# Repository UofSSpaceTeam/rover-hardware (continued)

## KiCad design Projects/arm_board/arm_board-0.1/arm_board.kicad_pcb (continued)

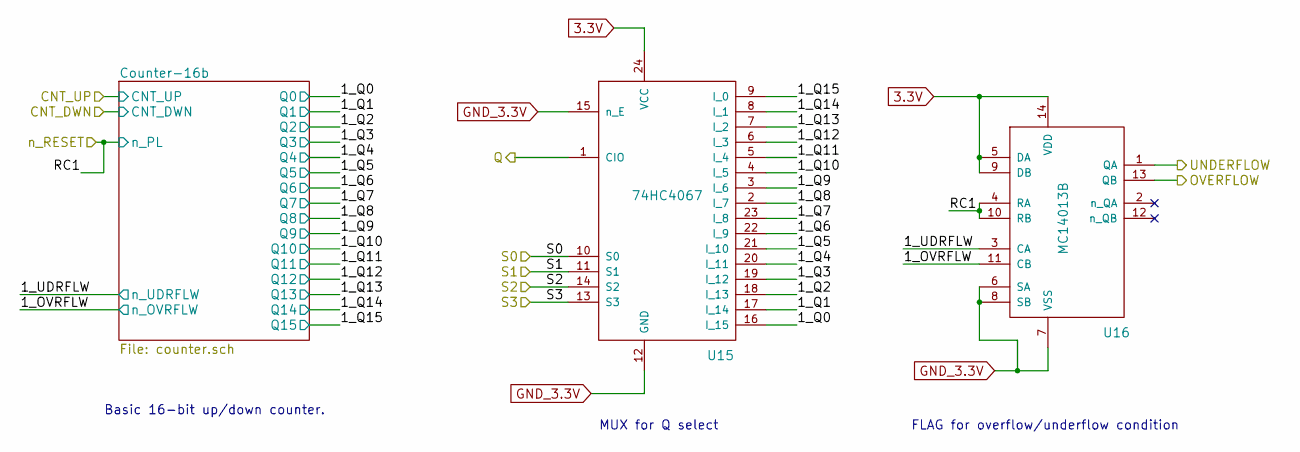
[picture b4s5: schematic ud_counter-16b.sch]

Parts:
U15: 74HC4067; SOIC-24
U49: MC14013B; SOIC-14_N

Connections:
/VNH3SP30 Motor SS 1/16-bit UD Counter/Counter-16b/Q0: U15.16 (I_15); also elsewhere on the board
/VNH3SP30 Motor SS 1/16-bit UD Counter/Counter-16b/Q1: U15.17 (I_14); also elsewhere on the board
/VNH3SP30 Motor SS 1/16-bit UD Counter/Counter-16b/Q2: U15.18 (I_13); also elsewhere on the board
/VNH3SP30 Motor SS 1/16-bit UD Counter/Counter-16b/Q3: U15.19 (I_12); also elsewhere on the board
/VNH3SP30 Motor SS 1/16-bit UD Counter/Counter-16b/Q4: U15.20 (I_11); also elsewhere on the board
/VNH3SP30 Motor SS 1/16-bit UD Counter/Counter-16b/Q5: U15.21 (I_10); also elsewhere on the board
/VNH3SP30 Motor SS 1/16-bit UD Counter/Counter-16b/Q6: U15.22 (I_9); also elsewhere on the board
/VNH3SP30 Motor SS 1/16-bit UD Counter/Counter-16b/Q7: U15.23 (I_8); also elsewhere on the board
/VNH3SP30 Motor SS 1/16-bit UD Counter/Counter-16b/Q8: U15.2 (I_7); also elsewhere on the board
/VNH3SP30 Motor SS 1/16-bit UD Counter/Counter-16b/Q9: U15.3 (I_6); also elsewhere on the board
/VNH3SP30 Motor SS 1/16-bit UD Counter/Counter-16b/Q10: U15.4 (I_5); also elsewhere on the board
/VNH3SP30 Motor SS 1/16-bit UD Counter/Counter-16b/Q11: U15.5 (I_4); also elsewhere on the board
/VNH3SP30 Motor SS 1/16-bit UD Counter/Counter-16b/Q12: U15.6 (I_3); also elsewhere on the board
/VNH3SP30 Motor SS 1/16-bit UD Counter/Counter-16b/Q13: U15.7 (I_2); also elsewhere on the board
/VNH3SP30 Motor SS 1/16-bit UD Counter/Counter-16b/Q14: U15.8 (I_1); also elsewhere on the board
/VNH3SP30 Motor SS 1/16-bit UD Counter/Counter-16b/Q15: U15.9 (I_0); also elsewhere on the board
/VNH3SP30 Motor SS 1/CNT_S0: U15.10 (S0); also elsewhere on the board
/VNH3SP30 Motor SS 1/CNT_S1: U15.11 (S1); also elsewhere on the board
/VNH3SP30 Motor SS 1/CNT_S2: U15.14 (S2); also elsewhere on the board
/VNH3SP30 Motor SS 1/CNT_S3: U15.13 (S3); also elsewhere on the board
/VNH3SP30 Motor SS 1/Q_CNT: U15.1 (CIO); also elsewhere on the board
/vnh3sp30_motorLinac_ss/16-bit UD Counter/Counter-16b/n_OVRFLW: U49.11 (CB); also elsewhere on the board
/vnh3sp30_motorLinac_ss/16-bit UD Counter/Counter-16b/n_UDRFLW: U49.3 (CA); also elsewhere on the board
/vnh3sp30_motorLinac_ss/CNT_OVRFLW: U49.13 (QB); also elsewhere on the board
/vnh3sp30_motorLinac_ss/CNT_UDRFLW: U49.1 (QA); also elsewhere on the board
/vnh3sp30_motorLinac_ss/n_CNT_RESET: U49.4 (RA), U49.10 (RB); also elsewhere on the board

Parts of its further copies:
U16, U23, U30, U37, U51: MC14013B; SOIC-14_N
U22, U29, U36, U43, U50: 74HC4067; SOIC-24

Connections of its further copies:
/VNH3SP30 Motor SS 1/16-bit UD Counter/Counter-16b/n_OVRFLW: U16.11 (CB); also elsewhere on the board
/VNH3SP30 Motor SS 1/16-bit UD Counter/Counter-16b/n_UDRFLW: U16.3 (CA); also elsewhere on the board
/VNH3SP30 Motor SS 1/CNT_OVRFLW: U16.13 (QB); also elsewhere on the board
/VNH3SP30 Motor SS 1/CNT_S0: U22.10 (S0), U29.10 (S0), U36.10 (S0), U43.10 (S0), U50.10 (S0); also elsewhere on the board
/VNH3SP30 Motor SS 1/CNT_S1: U22.11 (S1), U29.11 (S1), U36.11 (S1), U43.11 (S1), U50.11 (S1); also elsewhere on the board
/VNH3SP30 Motor SS 1/CNT_S2: U22.14 (S2), U29.14 (S2), U36.14 (S2), U43.14 (S2), U50.14 (S2); also elsewhere on the board
/VNH3SP30 Motor SS 1/CNT_S3: U22.13 (S3), U29.13 (S3), U36.13 (S3), U43.13 (S3), U50.13 (S3); also elsewhere on the board
/VNH3SP30 Motor SS 1/CNT_UDRFLW: U16.1 (QA); also elsewhere on the board
/VNH3SP30 Motor SS 1/n_CNT_RESET: U16.4 (RA), U16.10 (RB); also elsewhere on the board
/VNH3SP30 Motor SS 2/16-bit UD Counter/Counter-16b/Q0: U50.16 (I_15); also elsewhere on the board
/VNH3SP30 Motor SS 2/16-bit UD Counter/Counter-16b/Q1: U50.17 (I_14); also elsewhere on the board
/VNH3SP30 Motor SS 2/16-bit UD Counter/Counter-16b/Q2: U50.18 (I_13); also elsewhere on the board
/VNH3SP30 Motor SS 2/16-bit UD Counter/Counter-16b/Q3: U50.19 (I_12); also elsewhere on the board
/VNH3SP30 Motor SS 2/16-bit UD Counter/Counter-16b/Q4: U50.20 (I_11); also elsewhere on the board
/VNH3SP30 Motor SS 2/16-bit UD Counter/Counter-16b/Q5: U50.21 (I_10); also elsewhere on the board
/VNH3SP30 Motor SS 2/16-bit UD Counter/Counter-16b/Q6: U50.22 (I_9); also elsewhere on the board
/VNH3SP30 Motor SS 2/16-bit UD Counter/Counter-16b/Q7: U50.23 (I_8); also elsewhere on the board
/VNH3SP30 Motor SS 2/16-bit UD Counter/Counter-16b/Q8: U50.2 (I_7); also elsewhere on the board
/VNH3SP30 Motor SS 2/16-bit UD Counter/Counter-16b/Q9: U50.3 (I_6); also elsewhere on the board
/VNH3SP30 Motor SS 2/16-bit UD Counter/Counter-16b/Q10: U50.4 (I_5); also elsewhere on the board
/VNH3SP30 Motor SS 2/16-bit UD Counter/Counter-16b/Q11: U50.5 (I_4); also elsewhere on the board
/VNH3SP30 Motor SS 2/16-bit UD Counter/Counter-16b/Q12: U50.6 (I_3); also elsewhere on the board
/VNH3SP30 Motor SS 2/16-bit UD Counter/Counter-16b/Q13: U50.7 (I_2); also elsewhere on the board
/VNH3SP30 Motor SS 2/16-bit UD Counter/Counter-16b/Q14: U50.8 (I_1); also elsewhere on the board
/VNH3SP30 Motor SS 2/16-bit UD Counter/Counter-16b/Q15: U50.9 (I_0); also elsewhere on the board
/VNH3SP30 Motor SS 2/16-bit UD Counter/Counter-16b/n_OVRFLW: U51.11 (CB); also elsewhere on the board
/VNH3SP30 Motor SS 2/16-bit UD Counter/Counter-16b/n_UDRFLW: U51.3 (CA); also elsewhere on the board
/VNH3SP30 Motor SS 2/CNT_OVRFLW: U51.13 (QB); also elsewhere on the board
/VNH3SP30 Motor SS 2/CNT_UDRFLW: U51.1 (QA); also elsewhere on the board
/VNH3SP30 Motor SS 2/Q_CNT: U50.1 (CIO); also elsewhere on the board
/VNH3SP30 Motor SS 2/n_CNT_RESET: U51.4 (RA), U51.10 (RB); also elsewhere on the board
/VNH3SP30 Motor SS 3/16-bit UD Counter/Counter-16b/Q0: U22.16 (I_15); also elsewhere on the board
/VNH3SP30 Motor SS 3/16-bit UD Counter/Counter-16b/Q1: U22.17 (I_14); also elsewhere on the board
/VNH3SP30 Motor SS 3/16-bit UD Counter/Counter-16b/Q2: U22.18 (I_13); also elsewhere on the board
/VNH3SP30 Motor SS 3/16-bit UD Counter/Counter-16b/Q3: U22.19 (I_12); also elsewhere on the board
/VNH3SP30 Motor SS 3/16-bit UD Counter/Counter-16b/Q4: U22.20 (I_11); also elsewhere on the board
/VNH3SP30 Motor SS 3/16-bit UD Counter/Counter-16b/Q5: U22.21 (I_10); also elsewhere on the board
/VNH3SP30 Motor SS 3/16-bit UD Counter/Counter-16b/Q6: U22.22 (I_9); also elsewhere on the board
/VNH3SP30 Motor SS 3/16-bit UD Counter/Counter-16b/Q7: U22.23 (I_8); also elsewhere on the board
/VNH3SP30 Motor SS 3/16-bit UD Counter/Counter-16b/Q8: U22.2 (I_7); also elsewhere on the board
/VNH3SP30 Motor SS 3/16-bit UD Counter/Counter-16b/Q9: U22.3 (I_6); also elsewhere on the board
/VNH3SP30 Motor SS 3/16-bit UD Counter/Counter-16b/Q10: U22.4 (I_5); also elsewhere on the board
/VNH3SP30 Motor SS 3/16-bit UD Counter/Counter-16b/Q11: U22.5 (I_4); also elsewhere on the board
/VNH3SP30 Motor SS 3/16-bit UD Counter/Counter-16b/Q12: U22.6 (I_3); also elsewhere on the board
/VNH3SP30 Motor SS 3/16-bit UD Counter/Counter-16b/Q13: U22.7 (I_2); also elsewhere on the board
/VNH3SP30 Motor SS 3/16-bit UD Counter/Counter-16b/Q14: U22.8 (I_1); also elsewhere on the board
/VNH3SP30 Motor SS 3/16-bit UD Counter/Counter-16b/Q15: U22.9 (I_0); also elsewhere on the board
/VNH3SP30 Motor SS 3/16-bit UD Counter/Counter-16b/n_OVRFLW: U23.11 (CB); also elsewhere on the board
/VNH3SP30 Motor SS 3/16-bit UD Counter/Counter-16b/n_UDRFLW: U23.3 (CA); also elsewhere on the board
/VNH3SP30 Motor SS 3/CNT_OVRFLW: U23.13 (QB); also elsewhere on the board
/VNH3SP30 Motor SS 3/CNT_UDRFLW: U23.1 (QA); also elsewhere on the board
/VNH3SP30 Motor SS 3/Q_CNT: U22.1 (CIO); also elsewhere on the board
/VNH3SP30 Motor SS 3/n_CNT_RESET: U23.4 (RA), U23.10 (RB); also elsewhere on the board
/VNH3SP30 Motor SS 4/16-bit UD Counter/Counter-16b/Q0: U36.16 (I_15); also elsewhere on the board
/VNH3SP30 Motor SS 4/16-bit UD Counter/Counter-16b/Q1: U36.17 (I_14); also elsewhere on the board
/VNH3SP30 Motor SS 4/16-bit UD Counter/Counter-16b/Q2: U36.18 (I_13); also elsewhere on the board
/VNH3SP30 Motor SS 4/16-bit UD Counter/Counter-16b/Q3: U36.19 (I_12); also elsewhere on the board
/VNH3SP30 Motor SS 4/16-bit UD Counter/Counter-16b/Q4: U36.20 (I_11); also elsewhere on the board
/VNH3SP30 Motor SS 4/16-bit UD Counter/Counter-16b/Q5: U36.21 (I_10); also elsewhere on the board
/VNH3SP30 Motor SS 4/16-bit UD Counter/Counter-16b/Q6: U36.22 (I_9); also elsewhere on the board
/VNH3SP30 Motor SS 4/16-bit UD Counter/Counter-16b/Q7: U36.23 (I_8); also elsewhere on the board
/VNH3SP30 Motor SS 4/16-bit UD Counter/Counter-16b/Q8: U36.2 (I_7); also elsewhere on the board
/VNH3SP30 Motor SS 4/16-bit UD Counter/Counter-16b/Q9: U36.3 (I_6); also elsewhere on the board
/VNH3SP30 Motor SS 4/16-bit UD Counter/Counter-16b/Q10: U36.4 (I_5); also elsewhere on the board
/VNH3SP30 Motor SS 4/16-bit UD Counter/Counter-16b/Q11: U36.5 (I_4); also elsewhere on the board
/VNH3SP30 Motor SS 4/16-bit UD Counter/Counter-16b/Q12: U36.6 (I_3); also elsewhere on the board
/VNH3SP30 Motor SS 4/16-bit UD Counter/Counter-16b/Q13: U36.7 (I_2); also elsewhere on the board
/VNH3SP30 Motor SS 4/16-bit UD Counter/Counter-16b/Q14: U36.8 (I_1); also elsewhere on the board
/VNH3SP30 Motor SS 4/16-bit UD Counter/Counter-16b/Q15: U36.9 (I_0); also elsewhere on the board
/VNH3SP30 Motor SS 4/16-bit UD Counter/Counter-16b/n_OVRFLW: U37.11 (CB); also elsewhere on the board
/VNH3SP30 Motor SS 4/16-bit UD Counter/Counter-16b/n_UDRFLW: U37.3 (CA); also elsewhere on the board
/VNH3SP30 Motor SS 4/CNT_OVRFLW: U37.13 (QB); also elsewhere on the board
/VNH3SP30 Motor SS 4/CNT_UDRFLW: U37.1 (QA); also elsewhere on the board
/VNH3SP30 Motor SS 4/Q_CNT: U36.1 (CIO); also elsewhere on the board
/VNH3SP30 Motor SS 4/n_CNT_RESET: U37.4 (RA), U37.10 (RB); also elsewhere on the board
/VNH3SP30 Motor SS 5/16-bit UD Counter/Counter-16b/Q0: U29.16 (I_15); also elsewhere on the board
/VNH3SP30 Motor SS 5/16-bit UD Counter/Counter-16b/Q1: U29.17 (I_14); also elsewhere on the board
/VNH3SP30 Motor SS 5/16-bit UD Counter/Counter-16b/Q2: U29.18 (I_13); also elsewhere on the board
/VNH3SP30 Motor SS 5/16-bit UD Counter/Counter-16b/Q3: U29.19 (I_12); also elsewhere on the board
/VNH3SP30 Motor SS 5/16-bit UD Counter/Counter-16b/Q4: U29.20 (I_11); also elsewhere on the board
/VNH3SP30 Motor SS 5/16-bit UD Counter/Counter-16b/Q5: U29.21 (I_10); also elsewhere on the board
/VNH3SP30 Motor SS 5/16-bit UD Counter/Counter-16b/Q6: U29.22 (I_9); also elsewhere on the board
/VNH3SP30 Motor SS 5/16-bit UD Counter/Counter-16b/Q7: U29.23 (I_8); also elsewhere on the board
/VNH3SP30 Motor SS 5/16-bit UD Counter/Counter-16b/Q8: U29.2 (I_7); also elsewhere on the board
/VNH3SP30 Motor SS 5/16-bit UD Counter/Counter-16b/Q9: U29.3 (I_6); also elsewhere on the board
/VNH3SP30 Motor SS 5/16-bit UD Counter/Counter-16b/Q10: U29.4 (I_5); also elsewhere on the board
/VNH3SP30 Motor SS 5/16-bit UD Counter/Counter-16b/Q11: U29.5 (I_4); also elsewhere on the board
/VNH3SP30 Motor SS 5/16-bit UD Counter/Counter-16b/Q12: U29.6 (I_3); also elsewhere on the board
/VNH3SP30 Motor SS 5/16-bit UD Counter/Counter-16b/Q13: U29.7 (I_2); also elsewhere on the board
/VNH3SP30 Motor SS 5/16-bit UD Counter/Counter-16b/Q14: U29.8 (I_1); also elsewhere on the board
/VNH3SP30 Motor SS 5/16-bit UD Counter/Counter-16b/Q15: U29.9 (I_0); also elsewhere on the board
/VNH3SP30 Motor SS 5/16-bit UD Counter/Counter-16b/n_OVRFLW: U30.11 (CB); also elsewhere on the board
/VNH3SP30 Motor SS 5/16-bit UD Counter/Counter-16b/n_UDRFLW: U30.3 (CA); also elsewhere on the board
/VNH3SP30 Motor SS 5/CNT_OVRFLW: U30.13 (QB); also elsewhere on the board
/VNH3SP30 Motor SS 5/CNT_UDRFLW: U30.1 (QA); also elsewhere on the board
/VNH3SP30 Motor SS 5/Q_CNT: U29.1 (CIO); also elsewhere on the board
/VNH3SP30 Motor SS 5/n_CNT_RESET: U30.4 (RA), U30.10 (RB); also elsewhere on the board
/vnh3sp30_motorLinac_ss/16-bit UD Counter/Counter-16b/Q0: U43.16 (I_15); also elsewhere on the board
/vnh3sp30_motorLinac_ss/16-bit UD Counter/Counter-16b/Q1: U43.17 (I_14); also elsewhere on the board
/vnh3sp30_motorLinac_ss/16-bit UD Counter/Counter-16b/Q2: U43.18 (I_13); also elsewhere on the board
/vnh3sp30_motorLinac_ss/16-bit UD Counter/Counter-16b/Q3: U43.19 (I_12); also elsewhere on the board
/vnh3sp30_motorLinac_ss/16-bit UD Counter/Counter-16b/Q4: U43.20 (I_11); also elsewhere on the board
/vnh3sp30_motorLinac_ss/16-bit UD Counter/Counter-16b/Q5: U43.21 (I_10); also elsewhere on the board
/vnh3sp30_motorLinac_ss/16-bit UD Counter/Counter-16b/Q6: U43.22 (I_9); also elsewhere on the board
/vnh3sp30_motorLinac_ss/16-bit UD Counter/Counter-16b/Q7: U43.23 (I_8); also elsewhere on the board
/vnh3sp30_motorLinac_ss/16-bit UD Counter/Counter-16b/Q8: U43.2 (I_7); also elsewhere on the board
/vnh3sp30_motorLinac_ss/16-bit UD Counter/Counter-16b/Q9: U43.3 (I_6); also elsewhere on the board
/vnh3sp30_motorLinac_ss/16-bit UD Counter/Counter-16b/Q10: U43.4 (I_5); also elsewhere on the board
/vnh3sp30_motorLinac_ss/16-bit UD Counter/Counter-16b/Q11: U43.5 (I_4); also elsewhere on the board
/vnh3sp30_motorLinac_ss/16-bit UD Counter/Counter-16b/Q12: U43.6 (I_3); also elsewhere on the board
/vnh3sp30_motorLinac_ss/16-bit UD Counter/Counter-16b/Q13: U43.7 (I_2); also elsewhere on the board
/vnh3sp30_motorLinac_ss/16-bit UD Counter/Counter-16b/Q14: U43.8 (I_1); also elsewhere on the board
/vnh3sp30_motorLinac_ss/16-bit UD Counter/Counter-16b/Q15: U43.9 (I_0); also elsewhere on the board
/vnh3sp30_motorLinac_ss/Q_CNT: U43.1 (CIO); also elsewhere on the board

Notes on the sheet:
Basic 16-bit up/down counter.
MUX for Q select
FLAG for overflow/underflow condition

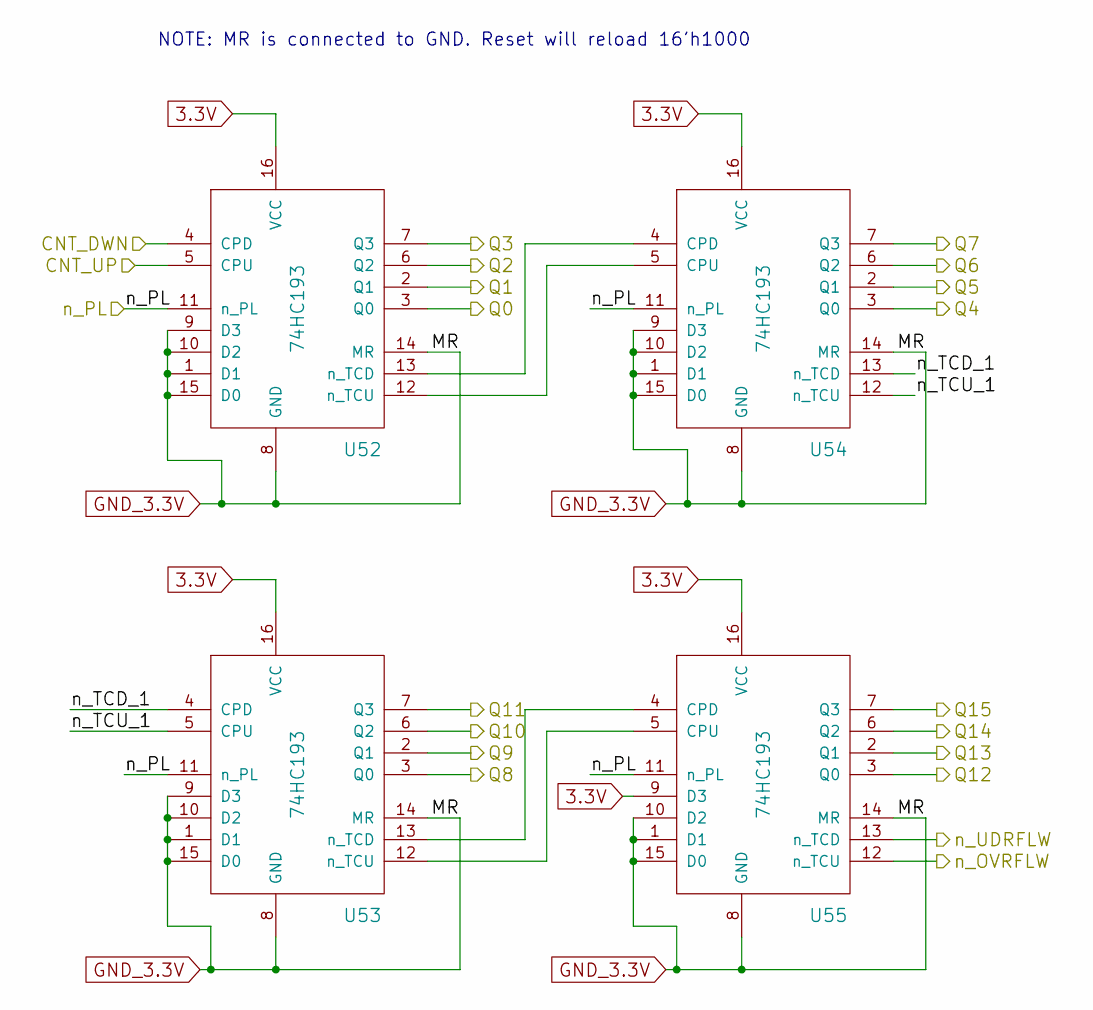
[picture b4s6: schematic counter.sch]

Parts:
U17, U18, U19, U20: 74HC193; SOIC-16

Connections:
/VNH3SP30 Motor SS 1/16-bit UD Counter/CNT_DWN: U17.4 (CPD); also elsewhere on the board
/VNH3SP30 Motor SS 1/16-bit UD Counter/CNT_UP: U17.5 (CPU); also elsewhere on the board
/VNH3SP30 Motor SS 1/16-bit UD Counter/Counter-16b/Q0: U17.3 (Q0); also elsewhere on the board
/VNH3SP30 Motor SS 1/16-bit UD Counter/Counter-16b/Q1: U17.2 (Q1); also elsewhere on the board
/VNH3SP30 Motor SS 1/16-bit UD Counter/Counter-16b/Q2: U17.6 (Q2); also elsewhere on the board
/VNH3SP30 Motor SS 1/16-bit UD Counter/Counter-16b/Q3: U17.7 (Q3); also elsewhere on the board
/VNH3SP30 Motor SS 1/16-bit UD Counter/Counter-16b/Q4: U19.3 (Q0); also elsewhere on the board
/VNH3SP30 Motor SS 1/16-bit UD Counter/Counter-16b/Q5: U19.2 (Q1); also elsewhere on the board
/VNH3SP30 Motor SS 1/16-bit UD Counter/Counter-16b/Q6: U19.6 (Q2); also elsewhere on the board
/VNH3SP30 Motor SS 1/16-bit UD Counter/Counter-16b/Q7: U19.7 (Q3); also elsewhere on the board
/VNH3SP30 Motor SS 1/16-bit UD Counter/Counter-16b/Q8: U18.3 (Q0); also elsewhere on the board
/VNH3SP30 Motor SS 1/16-bit UD Counter/Counter-16b/Q9: U18.2 (Q1); also elsewhere on the board
/VNH3SP30 Motor SS 1/16-bit UD Counter/Counter-16b/Q10: U18.6 (Q2); also elsewhere on the board
/VNH3SP30 Motor SS 1/16-bit UD Counter/Counter-16b/Q11: U18.7 (Q3); also elsewhere on the board
/VNH3SP30 Motor SS 1/16-bit UD Counter/Counter-16b/Q12: U20.3 (Q0); also elsewhere on the board
/VNH3SP30 Motor SS 1/16-bit UD Counter/Counter-16b/Q13: U20.2 (Q1); also elsewhere on the board
/VNH3SP30 Motor SS 1/16-bit UD Counter/Counter-16b/Q14: U20.6 (Q2); also elsewhere on the board
/VNH3SP30 Motor SS 1/16-bit UD Counter/Counter-16b/Q15: U20.7 (Q3); also elsewhere on the board
/VNH3SP30 Motor SS 1/16-bit UD Counter/Counter-16b/n_OVRFLW: U20.12 (n_TCU); also elsewhere on the board
/VNH3SP30 Motor SS 1/16-bit UD Counter/Counter-16b/n_TCD_1: U18.4 (CPD), U19.13 (n_TCD)
/VNH3SP30 Motor SS 1/16-bit UD Counter/Counter-16b/n_TCU_1: U18.5 (CPU), U19.12 (n_TCU)
/VNH3SP30 Motor SS 1/16-bit UD Counter/Counter-16b/n_UDRFLW: U20.13 (n_TCD); also elsewhere on the board
/VNH3SP30 Motor SS 1/n_CNT_RESET: U17.11 (n_PL), U18.11 (n_PL), U19.11 (n_PL), U20.11 (n_PL); also elsewhere on the board
unnamed: U17.12 (n_TCU), U19.5 (CPU)
unnamed: U17.13 (n_TCD), U19.4 (CPD)
unnamed: U18.12 (n_TCU), U20.5 (CPU)
unnamed: U18.13 (n_TCD), U20.4 (CPD)

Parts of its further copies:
U24, U25, U26, U27, U31, U32, U33, U34, U38, U39, U40, U41, U45, U46, U47, U48, U52, U53, U54, U55: 74HC193; SOIC-16

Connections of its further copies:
/VNH3SP30 Motor SS 2/16-bit UD Counter/CNT_DWN: U24.4 (CPD); also elsewhere on the board
/VNH3SP30 Motor SS 2/16-bit UD Counter/CNT_UP: U24.5 (CPU); also elsewhere on the board
/VNH3SP30 Motor SS 2/16-bit UD Counter/Counter-16b/Q0: U24.3 (Q0); also elsewhere on the board
/VNH3SP30 Motor SS 2/16-bit UD Counter/Counter-16b/Q1: U24.2 (Q1); also elsewhere on the board
/VNH3SP30 Motor SS 2/16-bit UD Counter/Counter-16b/Q2: U24.6 (Q2); also elsewhere on the board
/VNH3SP30 Motor SS 2/16-bit UD Counter/Counter-16b/Q3: U24.7 (Q3); also elsewhere on the board
/VNH3SP30 Motor SS 2/16-bit UD Counter/Counter-16b/Q4: U26.3 (Q0); also elsewhere on the board
/VNH3SP30 Motor SS 2/16-bit UD Counter/Counter-16b/Q5: U26.2 (Q1); also elsewhere on the board
/VNH3SP30 Motor SS 2/16-bit UD Counter/Counter-16b/Q6: U26.6 (Q2); also elsewhere on the board
/VNH3SP30 Motor SS 2/16-bit UD Counter/Counter-16b/Q7: U26.7 (Q3); also elsewhere on the board
/VNH3SP30 Motor SS 2/16-bit UD Counter/Counter-16b/Q8: U25.3 (Q0); also elsewhere on the board
/VNH3SP30 Motor SS 2/16-bit UD Counter/Counter-16b/Q9: U25.2 (Q1); also elsewhere on the board
/VNH3SP30 Motor SS 2/16-bit UD Counter/Counter-16b/Q10: U25.6 (Q2); also elsewhere on the board
/VNH3SP30 Motor SS 2/16-bit UD Counter/Counter-16b/Q11: U25.7 (Q3); also elsewhere on the board
/VNH3SP30 Motor SS 2/16-bit UD Counter/Counter-16b/Q12: U27.3 (Q0); also elsewhere on the board
/VNH3SP30 Motor SS 2/16-bit UD Counter/Counter-16b/Q13: U27.2 (Q1); also elsewhere on the board
/VNH3SP30 Motor SS 2/16-bit UD Counter/Counter-16b/Q14: U27.6 (Q2); also elsewhere on the board
/VNH3SP30 Motor SS 2/16-bit UD Counter/Counter-16b/Q15: U27.7 (Q3); also elsewhere on the board
/VNH3SP30 Motor SS 2/16-bit UD Counter/Counter-16b/n_OVRFLW: U27.12 (n_TCU); also elsewhere on the board
/VNH3SP30 Motor SS 2/16-bit UD Counter/Counter-16b/n_TCD_1: U25.4 (CPD), U26.13 (n_TCD)
/VNH3SP30 Motor SS 2/16-bit UD Counter/Counter-16b/n_TCU_1: U25.5 (CPU), U26.12 (n_TCU)
/VNH3SP30 Motor SS 2/16-bit UD Counter/Counter-16b/n_UDRFLW: U27.13 (n_TCD); also elsewhere on the board
/VNH3SP30 Motor SS 2/n_CNT_RESET: U24.11 (n_PL), U25.11 (n_PL), U26.11 (n_PL), U27.11 (n_PL); also elsewhere on the board
/VNH3SP30 Motor SS 3/16-bit UD Counter/CNT_DWN: U31.4 (CPD); also elsewhere on the board
/VNH3SP30 Motor SS 3/16-bit UD Counter/CNT_UP: U31.5 (CPU); also elsewhere on the board
/VNH3SP30 Motor SS 3/16-bit UD Counter/Counter-16b/Q0: U31.3 (Q0); also elsewhere on the board
/VNH3SP30 Motor SS 3/16-bit UD Counter/Counter-16b/Q1: U31.2 (Q1); also elsewhere on the board
/VNH3SP30 Motor SS 3/16-bit UD Counter/Counter-16b/Q2: U31.6 (Q2); also elsewhere on the board
/VNH3SP30 Motor SS 3/16-bit UD Counter/Counter-16b/Q3: U31.7 (Q3); also elsewhere on the board
/VNH3SP30 Motor SS 3/16-bit UD Counter/Counter-16b/Q4: U33.3 (Q0); also elsewhere on the board
/VNH3SP30 Motor SS 3/16-bit UD Counter/Counter-16b/Q5: U33.2 (Q1); also elsewhere on the board
/VNH3SP30 Motor SS 3/16-bit UD Counter/Counter-16b/Q6: U33.6 (Q2); also elsewhere on the board
/VNH3SP30 Motor SS 3/16-bit UD Counter/Counter-16b/Q7: U33.7 (Q3); also elsewhere on the board
/VNH3SP30 Motor SS 3/16-bit UD Counter/Counter-16b/Q8: U32.3 (Q0); also elsewhere on the board
/VNH3SP30 Motor SS 3/16-bit UD Counter/Counter-16b/Q9: U32.2 (Q1); also elsewhere on the board
/VNH3SP30 Motor SS 3/16-bit UD Counter/Counter-16b/Q10: U32.6 (Q2); also elsewhere on the board
/VNH3SP30 Motor SS 3/16-bit UD Counter/Counter-16b/Q11: U32.7 (Q3); also elsewhere on the board
/VNH3SP30 Motor SS 3/16-bit UD Counter/Counter-16b/Q12: U34.3 (Q0); also elsewhere on the board
/VNH3SP30 Motor SS 3/16-bit UD Counter/Counter-16b/Q13: U34.2 (Q1); also elsewhere on the board
/VNH3SP30 Motor SS 3/16-bit UD Counter/Counter-16b/Q14: U34.6 (Q2); also elsewhere on the board
/VNH3SP30 Motor SS 3/16-bit UD Counter/Counter-16b/Q15: U34.7 (Q3); also elsewhere on the board
/VNH3SP30 Motor SS 3/16-bit UD Counter/Counter-16b/n_OVRFLW: U34.12 (n_TCU); also elsewhere on the board
/VNH3SP30 Motor SS 3/16-bit UD Counter/Counter-16b/n_TCD_1: U32.4 (CPD), U33.13 (n_TCD)
/VNH3SP30 Motor SS 3/16-bit UD Counter/Counter-16b/n_TCU_1: U32.5 (CPU), U33.12 (n_TCU)
/VNH3SP30 Motor SS 3/16-bit UD Counter/Counter-16b/n_UDRFLW: U34.13 (n_TCD); also elsewhere on the board
/VNH3SP30 Motor SS 3/n_CNT_RESET: U31.11 (n_PL), U32.11 (n_PL), U33.11 (n_PL), U34.11 (n_PL); also elsewhere on the board
/VNH3SP30 Motor SS 4/16-bit UD Counter/CNT_DWN: U45.4 (CPD); also elsewhere on the board
/VNH3SP30 Motor SS 4/16-bit UD Counter/CNT_UP: U45.5 (CPU); also elsewhere on the board
/VNH3SP30 Motor SS 4/16-bit UD Counter/Counter-16b/Q0: U45.3 (Q0); also elsewhere on the board
/VNH3SP30 Motor SS 4/16-bit UD Counter/Counter-16b/Q1: U45.2 (Q1); also elsewhere on the board
/VNH3SP30 Motor SS 4/16-bit UD Counter/Counter-16b/Q2: U45.6 (Q2); also elsewhere on the board
/VNH3SP30 Motor SS 4/16-bit UD Counter/Counter-16b/Q3: U45.7 (Q3); also elsewhere on the board
/VNH3SP30 Motor SS 4/16-bit UD Counter/Counter-16b/Q4: U47.3 (Q0); also elsewhere on the board
/VNH3SP30 Motor SS 4/16-bit UD Counter/Counter-16b/Q5: U47.2 (Q1); also elsewhere on the board
/VNH3SP30 Motor SS 4/16-bit UD Counter/Counter-16b/Q6: U47.6 (Q2); also elsewhere on the board
/VNH3SP30 Motor SS 4/16-bit UD Counter/Counter-16b/Q7: U47.7 (Q3); also elsewhere on the board
/VNH3SP30 Motor SS 4/16-bit UD Counter/Counter-16b/Q8: U46.3 (Q0); also elsewhere on the board
/VNH3SP30 Motor SS 4/16-bit UD Counter/Counter-16b/Q9: U46.2 (Q1); also elsewhere on the board
/VNH3SP30 Motor SS 4/16-bit UD Counter/Counter-16b/Q10: U46.6 (Q2); also elsewhere on the board
/VNH3SP30 Motor SS 4/16-bit UD Counter/Counter-16b/Q11: U46.7 (Q3); also elsewhere on the board
/VNH3SP30 Motor SS 4/16-bit UD Counter/Counter-16b/Q12: U48.3 (Q0); also elsewhere on the board
/VNH3SP30 Motor SS 4/16-bit UD Counter/Counter-16b/Q13: U48.2 (Q1); also elsewhere on the board
/VNH3SP30 Motor SS 4/16-bit UD Counter/Counter-16b/Q14: U48.6 (Q2); also elsewhere on the board
/VNH3SP30 Motor SS 4/16-bit UD Counter/Counter-16b/Q15: U48.7 (Q3); also elsewhere on the board
/VNH3SP30 Motor SS 4/16-bit UD Counter/Counter-16b/n_OVRFLW: U48.12 (n_TCU); also elsewhere on the board
/VNH3SP30 Motor SS 4/16-bit UD Counter/Counter-16b/n_TCD_1: U46.4 (CPD), U47.13 (n_TCD)
/VNH3SP30 Motor SS 4/16-bit UD Counter/Counter-16b/n_TCU_1: U46.5 (CPU), U47.12 (n_TCU)
/VNH3SP30 Motor SS 4/16-bit UD Counter/Counter-16b/n_UDRFLW: U48.13 (n_TCD); also elsewhere on the board
/VNH3SP30 Motor SS 4/n_CNT_RESET: U45.11 (n_PL), U46.11 (n_PL), U47.11 (n_PL), U48.11 (n_PL); also elsewhere on the board
/VNH3SP30 Motor SS 5/16-bit UD Counter/CNT_DWN: U38.4 (CPD); also elsewhere on the board
/VNH3SP30 Motor SS 5/16-bit UD Counter/CNT_UP: U38.5 (CPU); also elsewhere on the board
/VNH3SP30 Motor SS 5/16-bit UD Counter/Counter-16b/Q0: U38.3 (Q0); also elsewhere on the board
/VNH3SP30 Motor SS 5/16-bit UD Counter/Counter-16b/Q1: U38.2 (Q1); also elsewhere on the board
/VNH3SP30 Motor SS 5/16-bit UD Counter/Counter-16b/Q2: U38.6 (Q2); also elsewhere on the board
/VNH3SP30 Motor SS 5/16-bit UD Counter/Counter-16b/Q3: U38.7 (Q3); also elsewhere on the board
/VNH3SP30 Motor SS 5/16-bit UD Counter/Counter-16b/Q4: U40.3 (Q0); also elsewhere on the board
/VNH3SP30 Motor SS 5/16-bit UD Counter/Counter-16b/Q5: U40.2 (Q1); also elsewhere on the board
/VNH3SP30 Motor SS 5/16-bit UD Counter/Counter-16b/Q6: U40.6 (Q2); also elsewhere on the board
/VNH3SP30 Motor SS 5/16-bit UD Counter/Counter-16b/Q7: U40.7 (Q3); also elsewhere on the board
/VNH3SP30 Motor SS 5/16-bit UD Counter/Counter-16b/Q8: U39.3 (Q0); also elsewhere on the board
/VNH3SP30 Motor SS 5/16-bit UD Counter/Counter-16b/Q9: U39.2 (Q1); also elsewhere on the board
/VNH3SP30 Motor SS 5/16-bit UD Counter/Counter-16b/Q10: U39.6 (Q2); also elsewhere on the board
/VNH3SP30 Motor SS 5/16-bit UD Counter/Counter-16b/Q11: U39.7 (Q3); also elsewhere on the board
/VNH3SP30 Motor SS 5/16-bit UD Counter/Counter-16b/Q12: U41.3 (Q0); also elsewhere on the board
/VNH3SP30 Motor SS 5/16-bit UD Counter/Counter-16b/Q13: U41.2 (Q1); also elsewhere on the board
/VNH3SP30 Motor SS 5/16-bit UD Counter/Counter-16b/Q14: U41.6 (Q2); also elsewhere on the board
/VNH3SP30 Motor SS 5/16-bit UD Counter/Counter-16b/Q15: U41.7 (Q3); also elsewhere on the board
/VNH3SP30 Motor SS 5/16-bit UD Counter/Counter-16b/n_OVRFLW: U41.12 (n_TCU); also elsewhere on the board
/VNH3SP30 Motor SS 5/16-bit UD Counter/Counter-16b/n_TCD_1: U39.4 (CPD), U40.13 (n_TCD)
/VNH3SP30 Motor SS 5/16-bit UD Counter/Counter-16b/n_TCU_1: U39.5 (CPU), U40.12 (n_TCU)
/VNH3SP30 Motor SS 5/16-bit UD Counter/Counter-16b/n_UDRFLW: U41.13 (n_TCD); also elsewhere on the board
/VNH3SP30 Motor SS 5/n_CNT_RESET: U38.11 (n_PL), U39.11 (n_PL), U40.11 (n_PL), U41.11 (n_PL); also elsewhere on the board
/vnh3sp30_motorLinac_ss/16-bit UD Counter/CNT_DWN: U52.4 (CPD); also elsewhere on the board
/vnh3sp30_motorLinac_ss/16-bit UD Counter/CNT_UP: U52.5 (CPU); also elsewhere on the board
/vnh3sp30_motorLinac_ss/16-bit UD Counter/Counter-16b/Q0: U52.3 (Q0); also elsewhere on the board
/vnh3sp30_motorLinac_ss/16-bit UD Counter/Counter-16b/Q1: U52.2 (Q1); also elsewhere on the board
/vnh3sp30_motorLinac_ss/16-bit UD Counter/Counter-16b/Q2: U52.6 (Q2); also elsewhere on the board
/vnh3sp30_motorLinac_ss/16-bit UD Counter/Counter-16b/Q3: U52.7 (Q3); also elsewhere on the board
/vnh3sp30_motorLinac_ss/16-bit UD Counter/Counter-16b/Q4: U54.3 (Q0); also elsewhere on the board
/vnh3sp30_motorLinac_ss/16-bit UD Counter/Counter-16b/Q5: U54.2 (Q1); also elsewhere on the board
/vnh3sp30_motorLinac_ss/16-bit UD Counter/Counter-16b/Q6: U54.6 (Q2); also elsewhere on the board
/vnh3sp30_motorLinac_ss/16-bit UD Counter/Counter-16b/Q7: U54.7 (Q3); also elsewhere on the board
/vnh3sp30_motorLinac_ss/16-bit UD Counter/Counter-16b/Q8: U53.3 (Q0); also elsewhere on the board
/vnh3sp30_motorLinac_ss/16-bit UD Counter/Counter-16b/Q9: U53.2 (Q1); also elsewhere on the board
/vnh3sp30_motorLinac_ss/16-bit UD Counter/Counter-16b/Q10: U53.6 (Q2); also elsewhere on the board
/vnh3sp30_motorLinac_ss/16-bit UD Counter/Counter-16b/Q11: U53.7 (Q3); also elsewhere on the board
/vnh3sp30_motorLinac_ss/16-bit UD Counter/Counter-16b/Q12: U55.3 (Q0); also elsewhere on the board
/vnh3sp30_motorLinac_ss/16-bit UD Counter/Counter-16b/Q13: U55.2 (Q1); also elsewhere on the board
/vnh3sp30_motorLinac_ss/16-bit UD Counter/Counter-16b/Q14: U55.6 (Q2); also elsewhere on the board
/vnh3sp30_motorLinac_ss/16-bit UD Counter/Counter-16b/Q15: U55.7 (Q3); also elsewhere on the board
/vnh3sp30_motorLinac_ss/16-bit UD Counter/Counter-16b/n_OVRFLW: U55.12 (n_TCU); also elsewhere on the board
/vnh3sp30_motorLinac_ss/16-bit UD Counter/Counter-16b/n_TCD_1: U53.4 (CPD), U54.13 (n_TCD)
/vnh3sp30_motorLinac_ss/16-bit UD Counter/Counter-16b/n_TCU_1: U53.5 (CPU), U54.12 (n_TCU)
/vnh3sp30_motorLinac_ss/16-bit UD Counter/Counter-16b/n_UDRFLW: U55.13 (n_TCD); also elsewhere on the board
/vnh3sp30_motorLinac_ss/n_CNT_RESET: U52.11 (n_PL), U53.11 (n_PL), U54.11 (n_PL), U55.11 (n_PL); also elsewhere on the board
unnamed: U24.12 (n_TCU), U26.5 (CPU)
unnamed: U24.13 (n_TCD), U26.4 (CPD)
unnamed: U25.12 (n_TCU), U27.5 (CPU)
unnamed: U25.13 (n_TCD), U27.4 (CPD)
unnamed: U31.12 (n_TCU), U33.5 (CPU)
unnamed: U31.13 (n_TCD), U33.4 (CPD)
unnamed: U32.12 (n_TCU), U34.5 (CPU)
unnamed: U32.13 (n_TCD), U34.4 (CPD)
unnamed: U38.12 (n_TCU), U40.5 (CPU)
unnamed: U38.13 (n_TCD), U40.4 (CPD)
unnamed: U39.12 (n_TCU), U41.5 (CPU)
unnamed: U39.13 (n_TCD), U41.4 (CPD)
unnamed: U45.12 (n_TCU), U47.5 (CPU)
unnamed: U45.13 (n_TCD), U47.4 (CPD)
unnamed: U46.12 (n_TCU), U48.5 (CPU)
unnamed: U46.13 (n_TCD), U48.4 (CPD)
unnamed: U52.12 (n_TCU), U54.5 (CPU)
unnamed: U52.13 (n_TCD), U54.4 (CPD)
unnamed: U53.12 (n_TCU), U55.5 (CPU)
unnamed: U53.13 (n_TCD), U55.4 (CPD)

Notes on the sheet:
NOTE: MR is connected to GND. Reset will reload 16'h1000

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
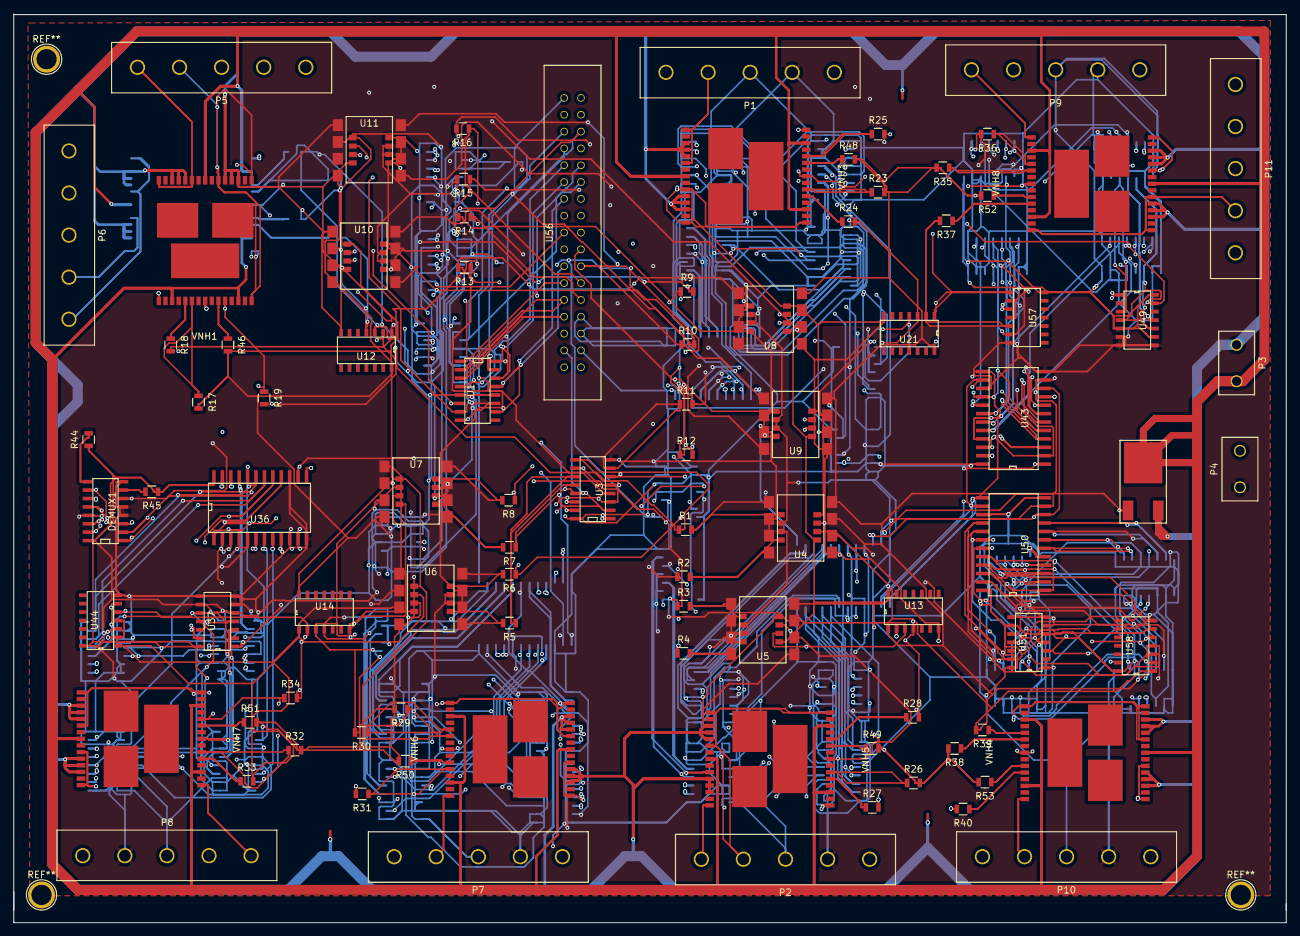
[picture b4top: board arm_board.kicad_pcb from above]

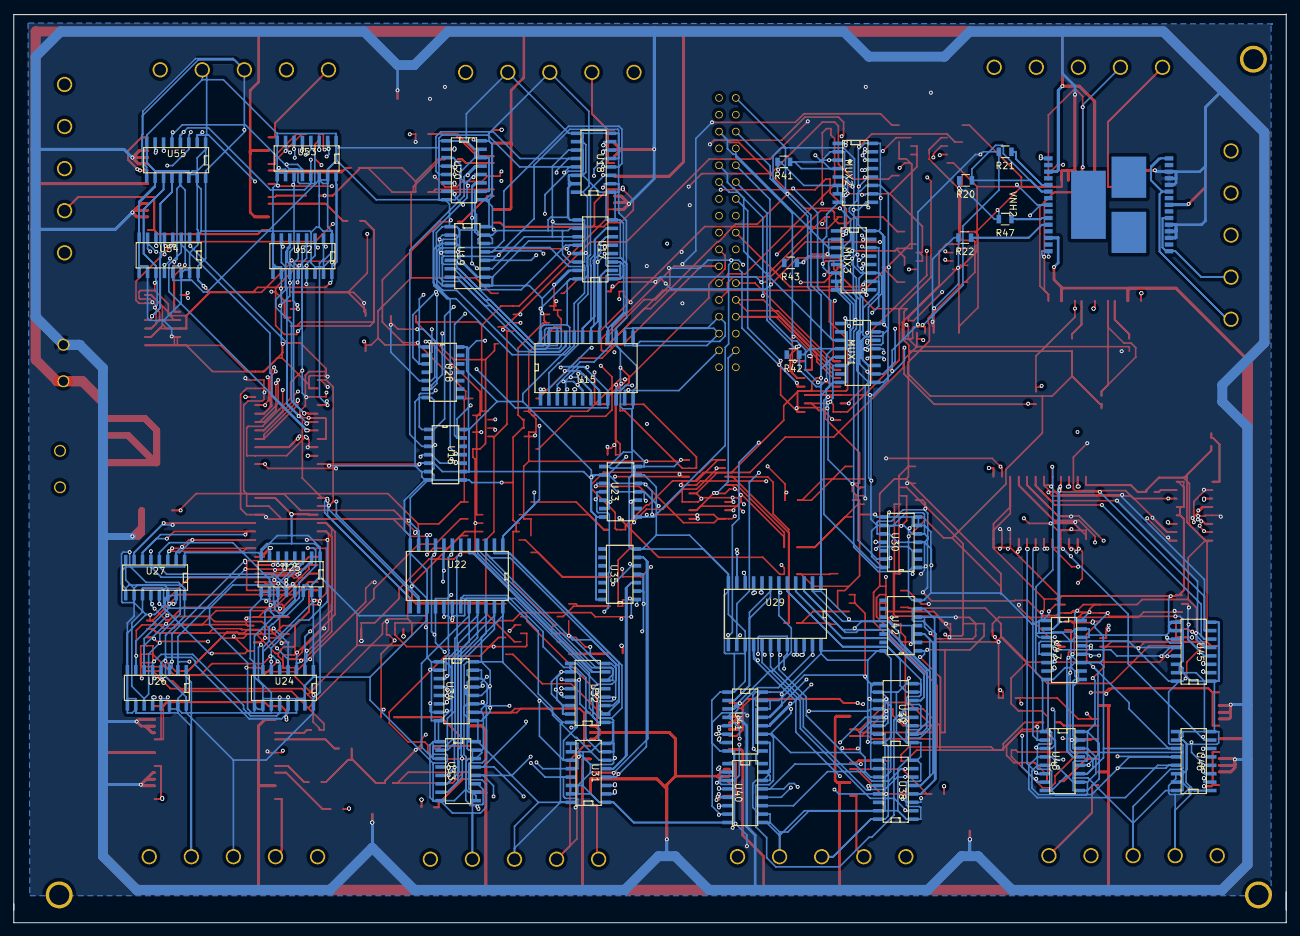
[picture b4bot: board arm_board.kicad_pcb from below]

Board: 4 copper layers, 192.0 x 137.2 mm, 142 parts (44 on the bottom side), 326 nets.

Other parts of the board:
P11: CONN_5; 5-pin_640467-1
R41, R42, R43, R44, R45: 1K; R_0805
R52: 4.7k; R_0805
U4#2, U5#2, U6#2, U7#2, U8#2, U9#2, U10#2, U11#2: TLP2160

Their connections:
/VNH3SP30 Motor SS 1/PWM: U11#2.6; also elsewhere on the board
/VNH3SP30 Motor SS 2/PWM: U4#2.6; also elsewhere on the board
/VNH3SP30 Motor SS 3/DIR: U5#2.7; also elsewhere on the board
/VNH3SP30 Motor SS 3/PWM: U5#2.6; also elsewhere on the board
/VNH3SP30 Motor SS 4/DIR: U6#2.7; also elsewhere on the board
/VNH3SP30 Motor SS 4/PWM: U6#2.6; also elsewhere on the board
/VNH3SP30 Motor SS 5/DIR: U7#2.7; also elsewhere on the board
/VNH3SP30 Motor SS 5/PWM: U7#2.6; also elsewhere on the board
/VNH3SP30 SS 1/DIR: U8#2.7; also elsewhere on the board
/VNH3SP30 SS 1/PWM: U8#2.6; also elsewhere on the board
/VNH3SP30 SS 2/DIR: U9#2.7; also elsewhere on the board
/VNH3SP30 SS 2/PWM: U9#2.6; also elsewhere on the board
/vnh3sp30_motorLinac_ss/DIR: U10#2.7; also elsewhere on the board
/vnh3sp30_motorLinac_ss/PWM: U10#2.6; also elsewhere on the board
/vnh3sp30_motorLinac_ss/WPR: P11.5; also elsewhere on the board
GND_12V: U4#2.5, U5#2.5, U6#2.5, U7#2.5, U8#2.5, U9#2.5, U10#2.5, U11#2.5; also elsewhere on the board
NOISE_5V: R52.2, U4#2.8, U5#2.8, U6#2.8, U7#2.8, U8#2.8, U9#2.8, U10#2.8, U11#2.8; also elsewhere on the board
unnamed 225: R45.2; also elsewhere on the board
unnamed 226: R44.2; also elsewhere on the board
unnamed 241: P11.1; also elsewhere on the board
unnamed 242: P11.2; also elsewhere on the board
unnamed 243: U4#2.1; also elsewhere on the board
unnamed 244: U4#2.4; also elsewhere on the board
unnamed 245: U5#2.1; also elsewhere on the board
unnamed 246: U5#2.4; also elsewhere on the board
unnamed 247: U6#2.1; also elsewhere on the board
unnamed 248: U6#2.4; also elsewhere on the board
unnamed 249: U7#2.1; also elsewhere on the board
unnamed 250: U7#2.4; also elsewhere on the board
unnamed 251: U10#2.1; also elsewhere on the board
unnamed 252: U10#2.4; also elsewhere on the board
unnamed 253: U11#2.1; also elsewhere on the board
unnamed 254: U11#2.4; also elsewhere on the board
unnamed 255: U8#2.1; also elsewhere on the board
unnamed 256: U8#2.4; also elsewhere on the board
unnamed 257: U9#2.1; also elsewhere on the board
unnamed 258: U9#2.4; also elsewhere on the board
Whiper_GND: P11.4; also elsewhere on the board
Whiper_V++: P11.3; also elsewhere on the board
